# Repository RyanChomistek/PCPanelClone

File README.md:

To install go to releases and download and run the installer

once installed it should automatically start. it will auto generate a file called MixerSettings.json in your documents folder
 - in the file there is an array of dials, the index in the array corresponds to the index of the dial
 - for each dial there are three properties, Color, Target, and Processes
   - Color: an array that has 3 ints representing the color of the dial led
   - Target what the dial does. currently there are three states
     - 0: target processes (there should be annother property named Processes on the object). This means that the mixer will set the volume of all of the listed processes
     - 1: Master, sets the master volume
     - 2: Device, sets the volume of a specific output device (not sure if this one works yet)
     - 3: focused, set the volume of the currently focused window
   - Processes: an array of process strings. if Target is set to 3, then it will use this list to find the processes it wants to change

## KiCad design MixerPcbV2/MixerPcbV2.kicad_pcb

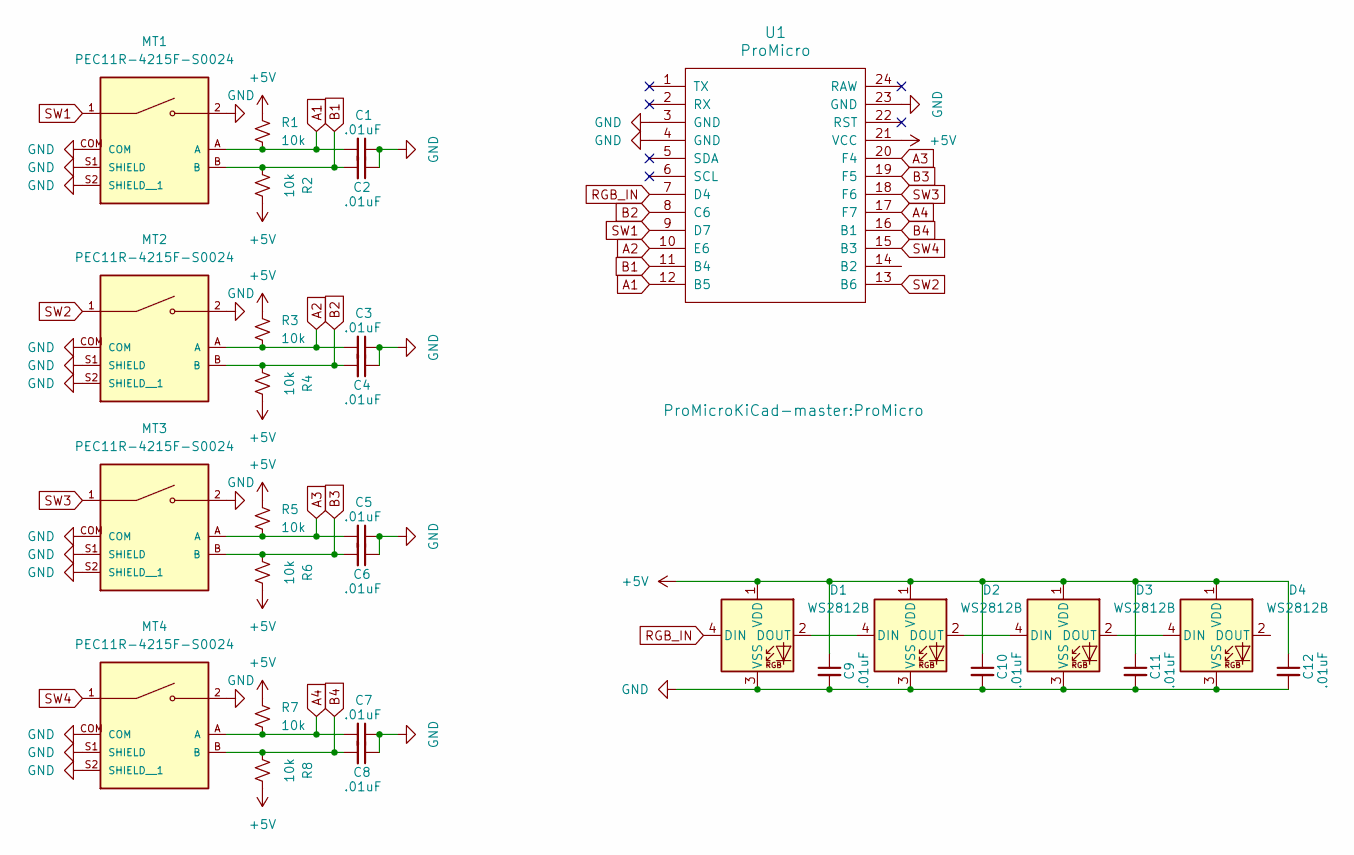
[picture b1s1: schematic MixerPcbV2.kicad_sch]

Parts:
C1, C2, C3, C4, C5, C6, C7, C8, C9, C10, C11, C12: .01uF; C_0805_2012Metric
D1, D2, D3, D4: WS2812B; LED_WS2812B_PLCC4_5.0x5.0mm_P3.2mm
MT1, MT2, MT3, MT4: PEC11R-4215F-S0024; XDCR_PEC11R-4215F-S0024; PARTREV Rev. 09/19
R1, R2, R3, R4, R5, R6, R7, R8: 10k; R_0805_2012Metric
U1: ProMicro

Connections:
+5V: C9.1, C10.1, C11.1, C12.1, D1.1 (VDD), D2.1 (VDD), D3.1 (VDD), D4.1 (VDD), R1.2, R2.1, R3.2, R4.1, R5.2, R6.1, R7.2, R8.1, U1.21 (VCC)
A1: C1.2, MT1.A, R1.1, U1.12 (B5)
A2: C3.2, MT2.A, R3.1, U1.10 (E6)
A3: C5.2, MT3.A, R5.1, U1.20 (F4)
A4: C7.2, MT4.A, R7.1, U1.17 (F7)
B1: C2.2, MT1.B, R2.2, U1.11 (B4)
B2: C4.2, MT2.B, R4.2, U1.8 (C6)
B3: C6.2, MT3.B, R6.2, U1.19 (F5)
B4: C8.2, MT4.B, R8.2, U1.16 (B1)
GND: C1.1, C2.1, C3.1, C4.1, C5.1, C6.1, C7.1, C8.1, C9.2, C10.2, C11.2, C12.2, D1.3 (VSS), D2.3 (VSS), D3.3 (VSS), D4.3 (VSS), MT1.2, MT1.COM, MT1.S1 (SHIELD), MT1.S2 (SHIELD__1), MT2.2, MT2.COM, MT2.S1 (SHIELD), MT2.S2 (SHIELD__1), MT3.2, MT3.COM, MT3.S1 (SHIELD), MT3.S2 (SHIELD__1), MT4.2, MT4.COM, MT4.S1 (SHIELD), MT4.S2 (SHIELD__1), U1.3 (GND), U1.4 (GND), U1.23 (GND)
unnamed: D1.2 (DOUT), D2.4 (DIN)
unnamed: D2.2 (DOUT), D3.4 (DIN)
unnamed: D3.2 (DOUT), D4.4 (DIN)
RGB_IN: D1.4 (DIN), U1.7 (D4)
SW1: MT1.1, U1.9 (D7)
SW2: MT2.1, U1.13 (B6)
SW3: MT3.1, U1.18 (F6)
SW4: MT4.1, U1.15 (B3)

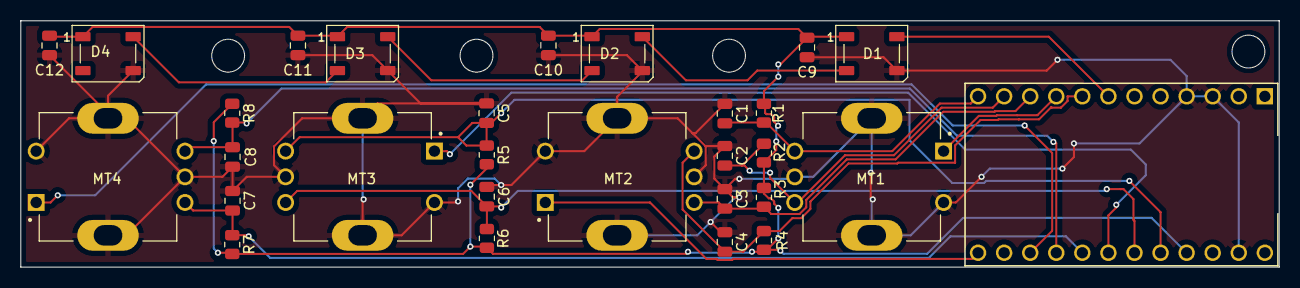
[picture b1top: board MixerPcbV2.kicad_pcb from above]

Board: 2 copper layers, 122.6 x 24.0 mm, 29 parts (0 on the bottom side), 18 nets.

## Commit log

2023-08-14 serial communicatio
2023-08-14 adding simple volume control
2023-08-15 adding settings parser and adding state to set master volume
2023-08-17 updating to handle lights
2023-08-28 refactoring
2023-10-01 adding new mixer controller
2023-10-10 got io extender working
2023-10-21 fixing new mixer device to work with client
2023-10-22 making new device code work with led signals
2024-03-13 cleanup
2024-03-17 updating to scan for available com port
2024-03-17 mostly working
2024-03-17 ignoring build folder
2024-03-17 fixing issues with printf and long int
2024-03-17 making the app run in the background
2024-03-17 changing timeout to be faster and less errors
2024-03-17 adding installer script
2024-03-17 removing old files
2024-03-17 renaming firmware file
2024-03-18 fixing issue with reading next command blocking
2024-03-18 adding led flash for current dial
2024-03-18 changing default led settings
2024-04-04 disabling logging via bool and fixing leaks
2024-04-04 making the main loop not exit if HrReadLoop fails
2024-04-06 refactoring iterating sessions
2024-04-06 adding mute buttons
2024-04-07 ignoring firmare build files
2024-04-07 adding debounce to switch
2024-04-07 resetting everything back to a good build state
2024-04-07 removing comment
2024-04-07 changing installer script to kill process before copying data
2024-04-07 fixing a couple issues with fetching process string
2024-04-08 fixing issues with the nSize carrying over from the last string query
2024-04-09 making mute now toggle LED
2024-04-10 adding mute state query on heatbeat to check all mute states
2025-08-27 starting switchover to HID
2025-08-29 improved hid handling
2025-08-30 updating to work with out reports
2025-09-13 updating to more hid stuff
2025-09-28 fixing leak
2026-06-01 updating ignore
2026-06-01 adding linux version
2026-06-01 updating
